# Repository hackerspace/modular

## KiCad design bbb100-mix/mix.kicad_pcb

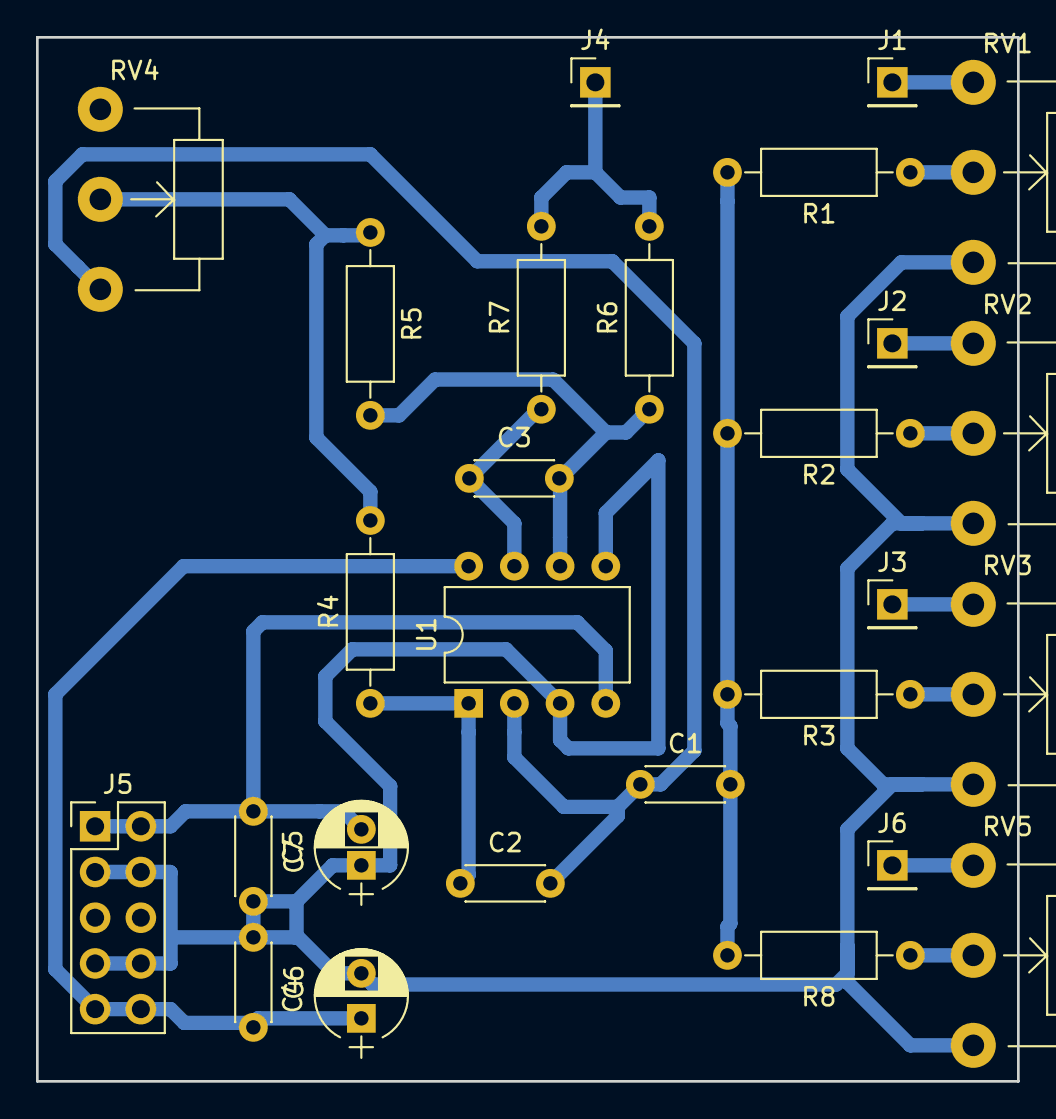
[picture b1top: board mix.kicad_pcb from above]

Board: 2 copper layers, 54.5 x 58.0 mm, 27 parts (0 on the bottom side), 18 nets.

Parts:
C1: 470n; C_Disc_D4.3mm_W1.9mm_P5.00mm
C2, C3: 47pF; C_Disc_D4.3mm_W1.9mm_P5.00mm
C4: 10u; CP_Radial_D5.0mm_P2.50mm
C5: 10u; CP_Radial_D5.0mm_P2.00mm
C6, C7: 100n; C_Disc_D4.3mm_W1.9mm_P5.00mm
J1, J2, J3, J4, J6: Conn_01x01; Pin_Header_Straight_1x01_Pitch2.54mm
J5: Conn_02x05_Odd_Even; Pin_Header_Straight_2x05_Pitch2.54mm
R1, R2, R3, R5, R6, R8: 100k; R_Axial_DIN0207_L6.3mm_D2.5mm_P10.16mm_Horizontal
R4, R7: 330; R_Axial_DIN0207_L6.3mm_D2.5mm_P10.16mm_Horizontal
RV1, RV2, RV3, RV4, RV5: 100k Lin; Potentiometer_WirePads
U1: TL072; DIP-8_W7.62mm

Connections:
+15V: C4.1, C6.2, J5.9, J5.10, U1.8
-15V: C5.2, C7.1, J5.1, J5.2, U1.4
/OUT: J4.1, R6.2, R7.2
GND: C4.2, C5.1, C6.1, C7.2, J5.3, J5.4, J5.7, J5.8, RV1.3, RV2.3, RV3.3, RV5.3, U1.3, U1.5
unnamed: C1.1, C2.2, RV4.3, U1.2
unnamed: C1.2, R1.2, R2.2, R3.2, R8.2
unnamed: C2.1, R4.1, U1.1
unnamed: C3.1, R7.1, U1.7
unnamed: C3.2, R5.2, R6.1, U1.6
unnamed: J1.1, RV1.1
unnamed: J2.1, RV2.1
unnamed: J3.1, RV3.1
unnamed: J6.1, RV5.1
unnamed: R1.1, RV1.2
unnamed: R2.1, RV2.2
unnamed: R3.1, RV3.2
unnamed: R4.2, R5.1, RV4.2
unnamed: R8.1, RV5.2

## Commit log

2018-04-25 psu schematic
2018-05-03 psu board
2018-06-18 rail
2018-06-18 side
2018-06-18 case
2018-06-18 sides milling
2018-06-20 psu panel
2018-06-20 more panel
2018-08-08 add mix panel
2018-12-29 narrow psu panel
2019-01-02 narrow psu panel gcode
2019-02-04 add gitignore
2019-02-04 add bbb100-mix
2019-02-08 output module schema
2019-02-08 output module schema again
2019-02-08 output: dc block
2019-02-08 output: zener diodes
2019-02-08 output: tweaks and fixes
2019-02-26 output: some changes
